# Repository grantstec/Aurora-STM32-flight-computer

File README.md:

# Aurora-STM32-flight-computer

## TO-DO
1. Finalize Parts List
2. Begin Schematic
3. Import OSH park pcb settings into KiCAD
4. Footprint demensions
5. Assemble footprint/layout
6. Traces
7. 3d Model?

## Resources
OSH park pcb setup link: https://github.com/grantstec/Aurora-STM32-flight-computer.git

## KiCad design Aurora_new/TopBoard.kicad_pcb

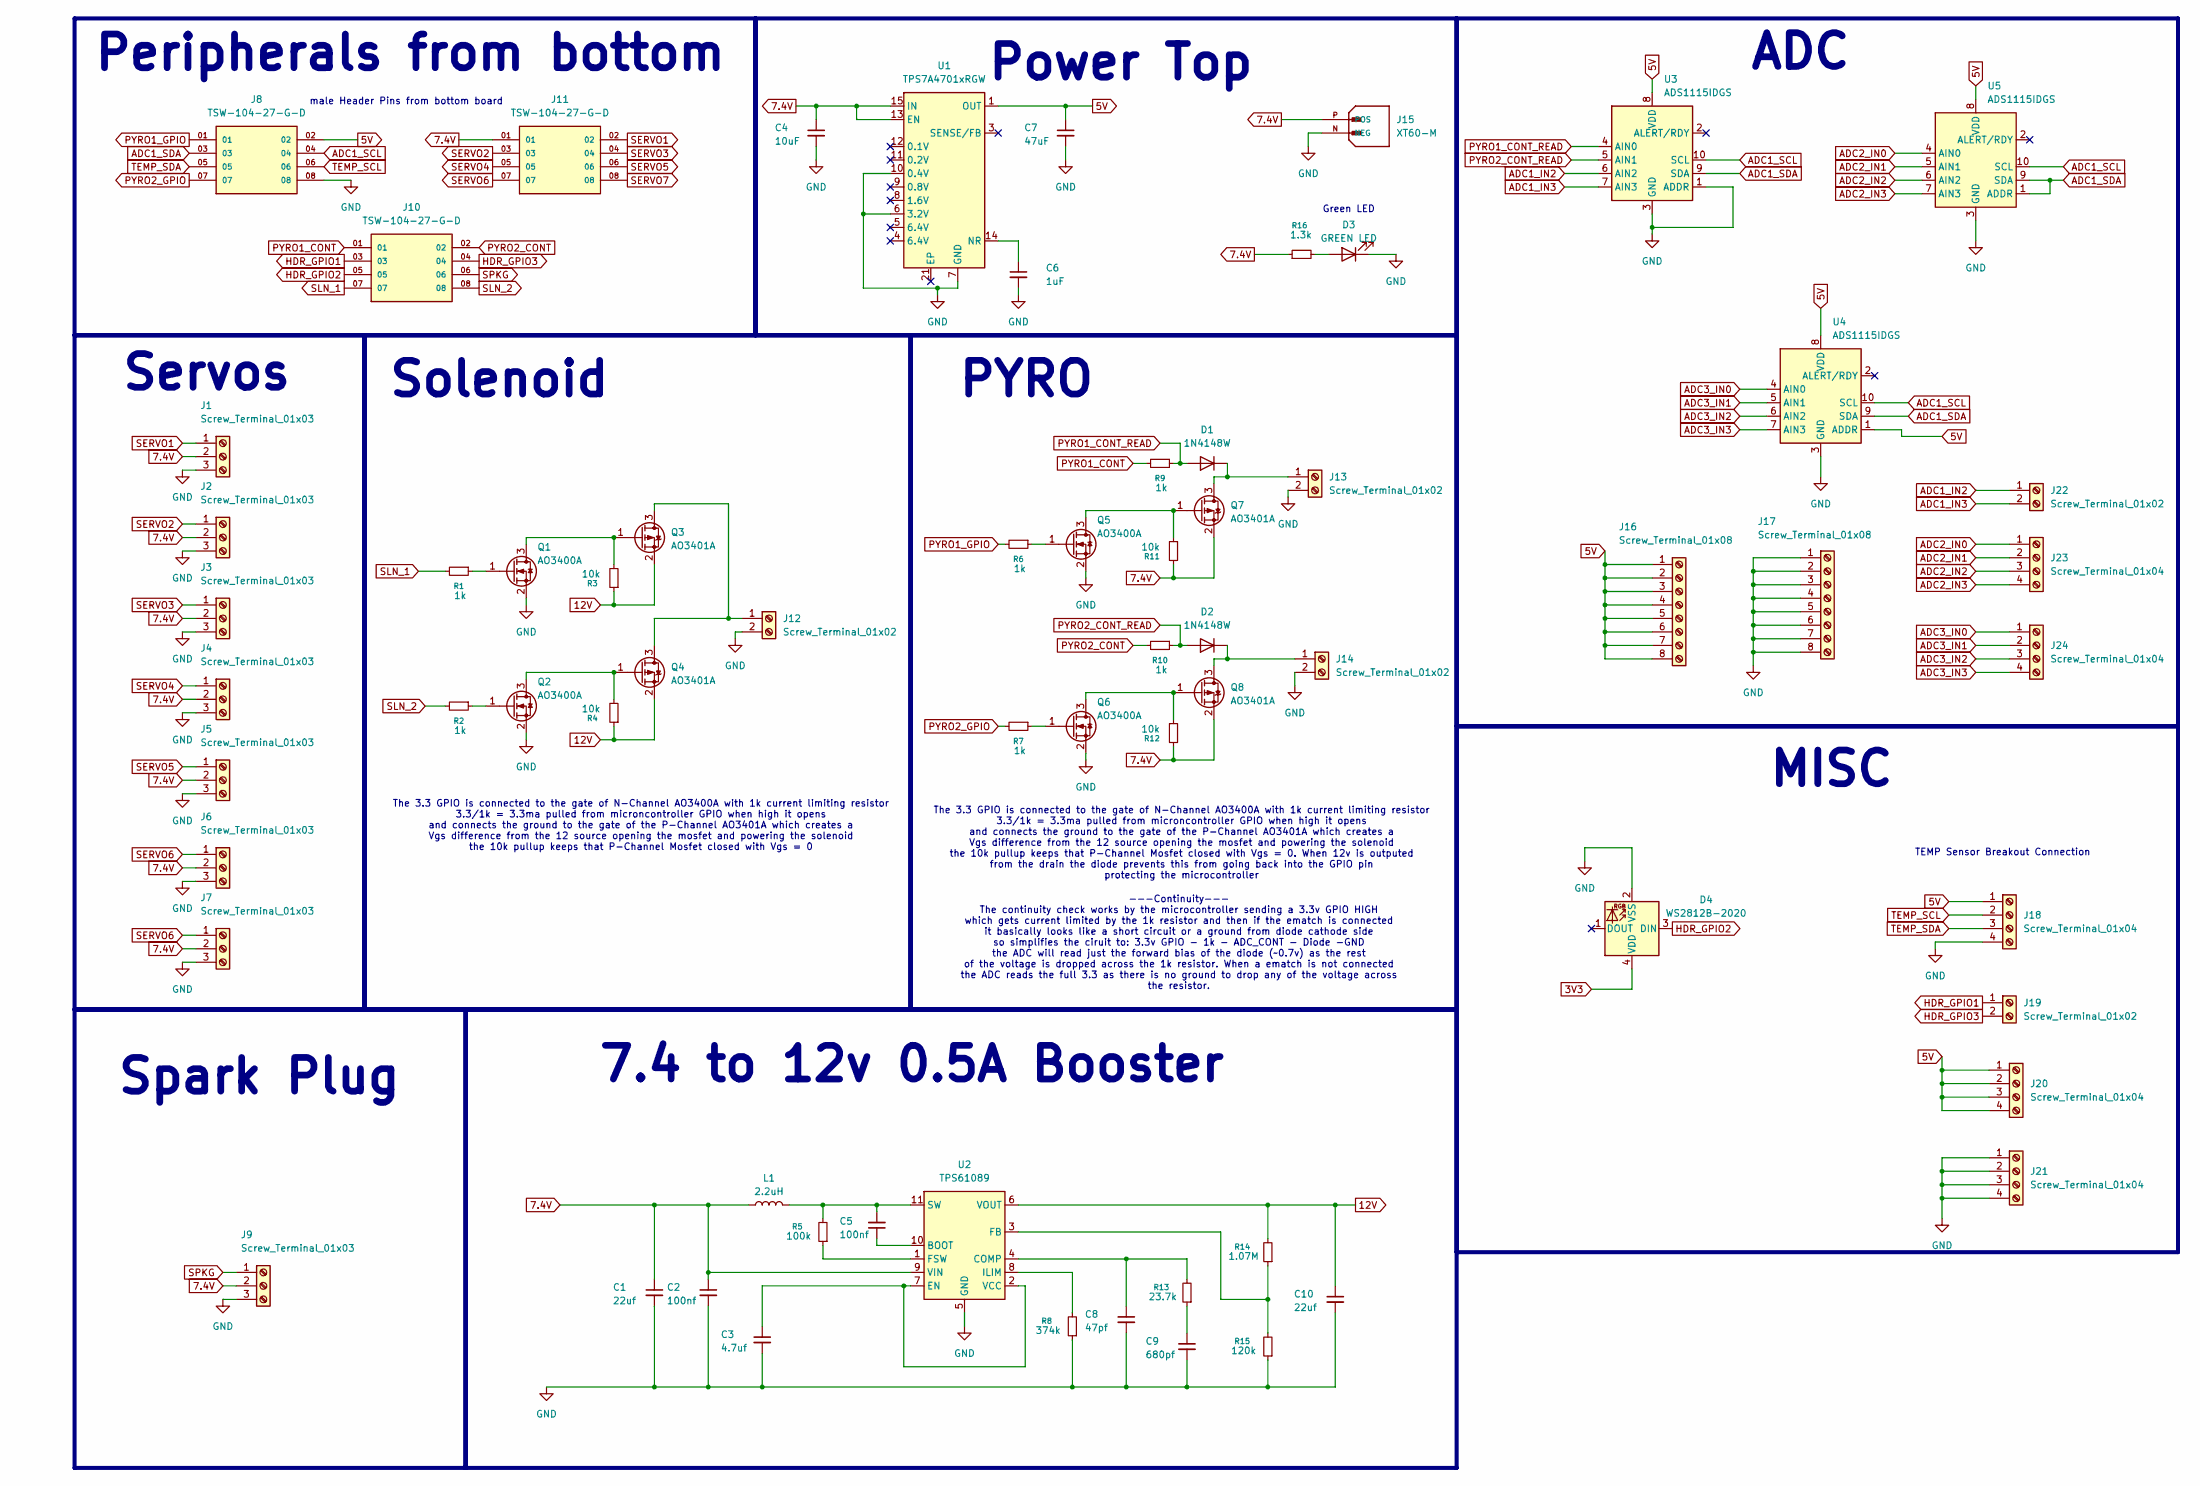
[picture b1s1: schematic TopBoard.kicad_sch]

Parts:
C1, C10: 22uf; C_0805_2012Metric
C2, C5: 100nf; C_0805_2012Metric
C3: 4.7uf; C_0805_2012Metric
C4: 10uF; C_0805_2012Metric
C6: 1uF; C_0805_2012Metric
C7: 47uF; C_0805_2012Metric
C8: 47pf; C_0805_2012Metric
C9: 680pf; C_0805_2012Metric
D1, D2: 1N4148W; D_SOD-123
D3: GREEN LED; LED_Cree-PLCC4_5x5mm_CW
D4: WS2812B-2020; LED_WS2812B-2020_PLCC4_2.0x2.0mm
J1, J2, J3, J4, J5, J6, J7, J9: Screw_Terminal_01x03; PHOENIX_1935174
J8, J10, J11: TSW-104-27-G-D; SAMTEC_TSW-104-27-G-D; PARTREV R
J12, J13, J14, J19, J22: Screw_Terminal_01x02; CONN_1729128_PXC
J15: XT60-M; AMASS_XT60-M; PARTREV V1.2
J16, J17: Screw_Terminal_01x08; CONN_1715789_PXC
J18, J20, J21, J23, J24: Screw_Terminal_01x04; CONN_1715747_PXC
L1: 2.2uH; L_0805_2012Metric
Q1, Q2, Q5, Q6: AO3400A; SOT-23
Q3, Q4, Q7, Q8: AO3401A; SOT-23
R1, R2, R6, R7, R9, R10: 1k; R_0805_2012Metric
R3, R4, R11, R12: 10k; R_0805_2012Metric
R5: 100k; R_0805_2012Metric
R8: 374k; R_0805_2012Metric
R13: 23.7k; R_0805_2012Metric
R14: 1.07M; R_0805_2012Metric
R15: 120k; R_0805_2012Metric
R16: 1.3k; R_0805_2012Metric
U1: TPS7A4701xRGW; Texas_RGW0020A_VQFN-20-1EP_5x5mm_P0.65mm_EP3.15x3.15mm
U2: TPS61089; Texas_VQFN-RNR0011A-11
U3, U4, U5: ADS1115IDGS; TSSOP-10_3x3mm_P0.5mm

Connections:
3V3: D4.4 (VDD)
5V: C7.1, J8.02, J16.1, J16.2, J16.3, J16.4, J16.5, J16.6, J16.7, J16.8, J18.1, J20.1, J20.2, J20.3, J20.4, U1.1 (OUT), U1.20 (OUT), U3.8 (VDD), U4.1 (ADDR), U4.8 (VDD), U5.8 (VDD)
7.4V: C1.1, C2.1, C4.1, J1.2, J2.2, J3.2, J4.2, J5.2, J6.2, J7.2, J9.2, J11.01, J15.P (POS), L1.1, Q7.2 (S), Q8.2 (S), R11.1, R12.1, R16.1, U1.13 (EN), U1.15 (IN), U1.16 (IN), U2.9 (VIN)
12V: C10.1, Q3.2 (S), Q4.2 (S), R3.1, R4.1, R14.2, U2.6 (VOUT)
ADC1_IN2: J22.1, U3.6 (AIN2)
ADC1_IN3: J22.2, U3.7 (AIN3)
ADC1_SCL: J8.04, U3.10 (SCL), U4.10 (SCL), U5.10 (SCL)
ADC1_SDA: J8.03, U3.9 (SDA), U4.9 (SDA), U5.1 (ADDR), U5.9 (SDA)
ADC2_IN0: J23.1, U5.4 (AIN0)
ADC2_IN1: J23.2, U5.5 (AIN1)
ADC2_IN2: J23.3, U5.6 (AIN2)
ADC2_IN3: J23.4, U5.7 (AIN3)
ADC3_IN0: J24.1, U4.4 (AIN0)
ADC3_IN1: J24.2, U4.5 (AIN1)
ADC3_IN2: J24.3, U4.6 (AIN2)
ADC3_IN3: J24.4, U4.7 (AIN3)
GND: C1.2, C2.2, C3.2, C4.2, C6.2, C7.2, C8.2, C9.2, C10.2, D3.1 (K), D4.2 (VSS), J1.3, J2.3, J3.3, J4.3, J5.3, J6.3, J7.3, J8.08, J9.3, J12.2, J13.2, J14.2, J15.N (NEG), J17.1, J17.2, J17.3, J17.4, J17.5, J17.6, J17.7, J17.8, J18.4, J21.1, J21.2, J21.3, J21.4, Q1.2 (S), Q2.2 (S), Q5.2 (S), Q6.2 (S), R8.1, R15.1, U1.6 (3.2V), U1.7 (GND), U1.10 (0.4V), U2.5 (GND), U3.1 (ADDR), U3.3 (GND), U4.3 (GND), U5.3 (GND)
HDR_GPIO1: J10.03, J19.1
HDR_GPIO2: D4.3 (DIN), J10.05
HDR_GPIO3: J10.04, J19.2
unnamed: C9.1, R13.1
unnamed: D1.1 (K), J13.1, Q7.3 (D)
unnamed: D2.1 (K), J14.1, Q8.3 (D)
unnamed: D3.2 (A), R16.2
unnamed: J12.1, Q3.3 (D), Q4.3 (D)
unnamed: Q1.3 (D), Q3.1 (G), R3.2
unnamed: Q1.1 (G), R1.1
unnamed: Q2.3 (D), Q4.1 (G), R4.2
unnamed: Q2.1 (G), R2.1
unnamed: Q5.3 (D), Q7.1 (G), R11.2
unnamed: Q5.1 (G), R6.1
unnamed: Q6.3 (D), Q8.1 (G), R12.2
unnamed: Q6.1 (G), R7.1
unnamed: C6.1, U1.14 (NR)
unnamed: C5.1, U2.10 (BOOT)
unnamed: C8.1, R13.2, U2.4 (COMP)
unnamed: C3.1, U2.2 (VCC), U2.7 (EN)
unnamed: R14.1, R15.2, U2.3 (FB)
unnamed: R5.1, U2.1 (FSW)
unnamed: R8.2, U2.8 (ILIM)
unnamed: C5.2, L1.2, R5.2, U2.11 (SW)
PYRO1_CONT: J10.01, R9.2
PYRO1_CONT_READ: D1.2 (A), R9.1, U3.4 (AIN0)
PYRO1_GPIO: J8.01, R6.2
PYRO2_CONT: J10.02, R10.2
PYRO2_CONT_READ: D2.2 (A), R10.1, U3.5 (AIN1)
PYRO2_GPIO: J8.07, R7.2
SERVO1: J1.1, J11.02
SERVO2: J2.1, J11.03
SERVO3: J3.1, J11.04
SERVO4: J4.1, J11.05
SERVO5: J5.1, J11.06
SERVO6: J6.1, J7.1, J11.07
SERVO7: J11.08
SLN_1: J10.07, R1.2
SLN_2: J10.08, R2.2
SPKG: J9.1, J10.06
TEMP_SCL: J8.06, J18.2
TEMP_SDA: J8.05, J18.3

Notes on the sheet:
ADC
Power Top
MISC
male Header Pins from bottom board
The 3.3 GPIO is connected to the gate of N-Channel AO3400A with 1k current limiting resistor 3.3/1k = 3.3ma pulled from microncontroller GPIO when high it opens and connects the ground to the gate of the P-Channel AO3401A which creates a Vgs difference from the 12 source opening the mosfet and powe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
Peripherals from bottom
PYRO
TEMP Sensor Breakout Connection
Spark Plug
The 3.3 GPIO is connected to the gate of N-Channel AO3400A with 1k current limiting resistor 3.3/1k = 3.3ma pulled from microncontroller GPIO when high it opens and connects the ground to the gate of the P-Channel AO3401A which creates a Vgs difference from the 12 source opening the mosfet and powe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
---Continuity--- The continuity check works by the microcontroller sending a 3.3v GPIO HIGH which gets current limited by the 1k resistor and then if the ematch is connected it basically looks like a short circuit or a ground from diode cathode side so simplifies the ciruit to: 3.3v GPIO - 1k - ADC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
Green LED
7.4 to 12v 0.5A Booster
Solenoid
Servos

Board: 2 copper layers, 68 parts (0 on the bottom side), 57 nets, no tracks yet.

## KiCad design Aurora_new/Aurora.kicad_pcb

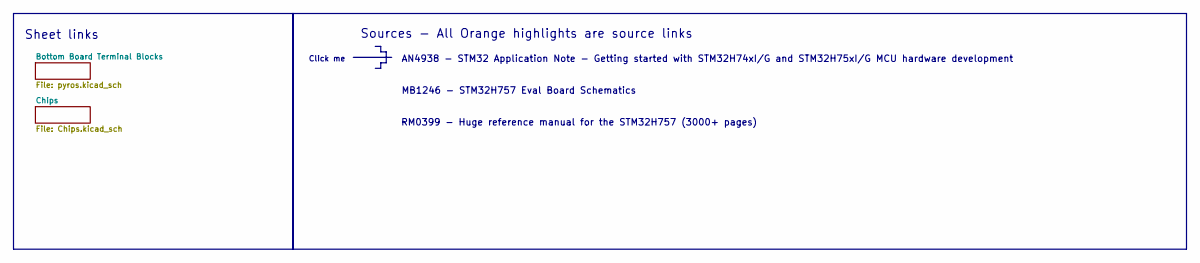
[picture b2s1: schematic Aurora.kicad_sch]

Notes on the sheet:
RM0399 - Huge reference manual for the STM32H757 (3000+ pages)
AN4938 - STM32 Application Note - Getting started with STM32H74xI/G and STM32H75xI/G MCU hardware development
MB1246 - STM32H757 Eval Board Schematics
Sheet links
Sources - All Orange highlights are source links
Click me

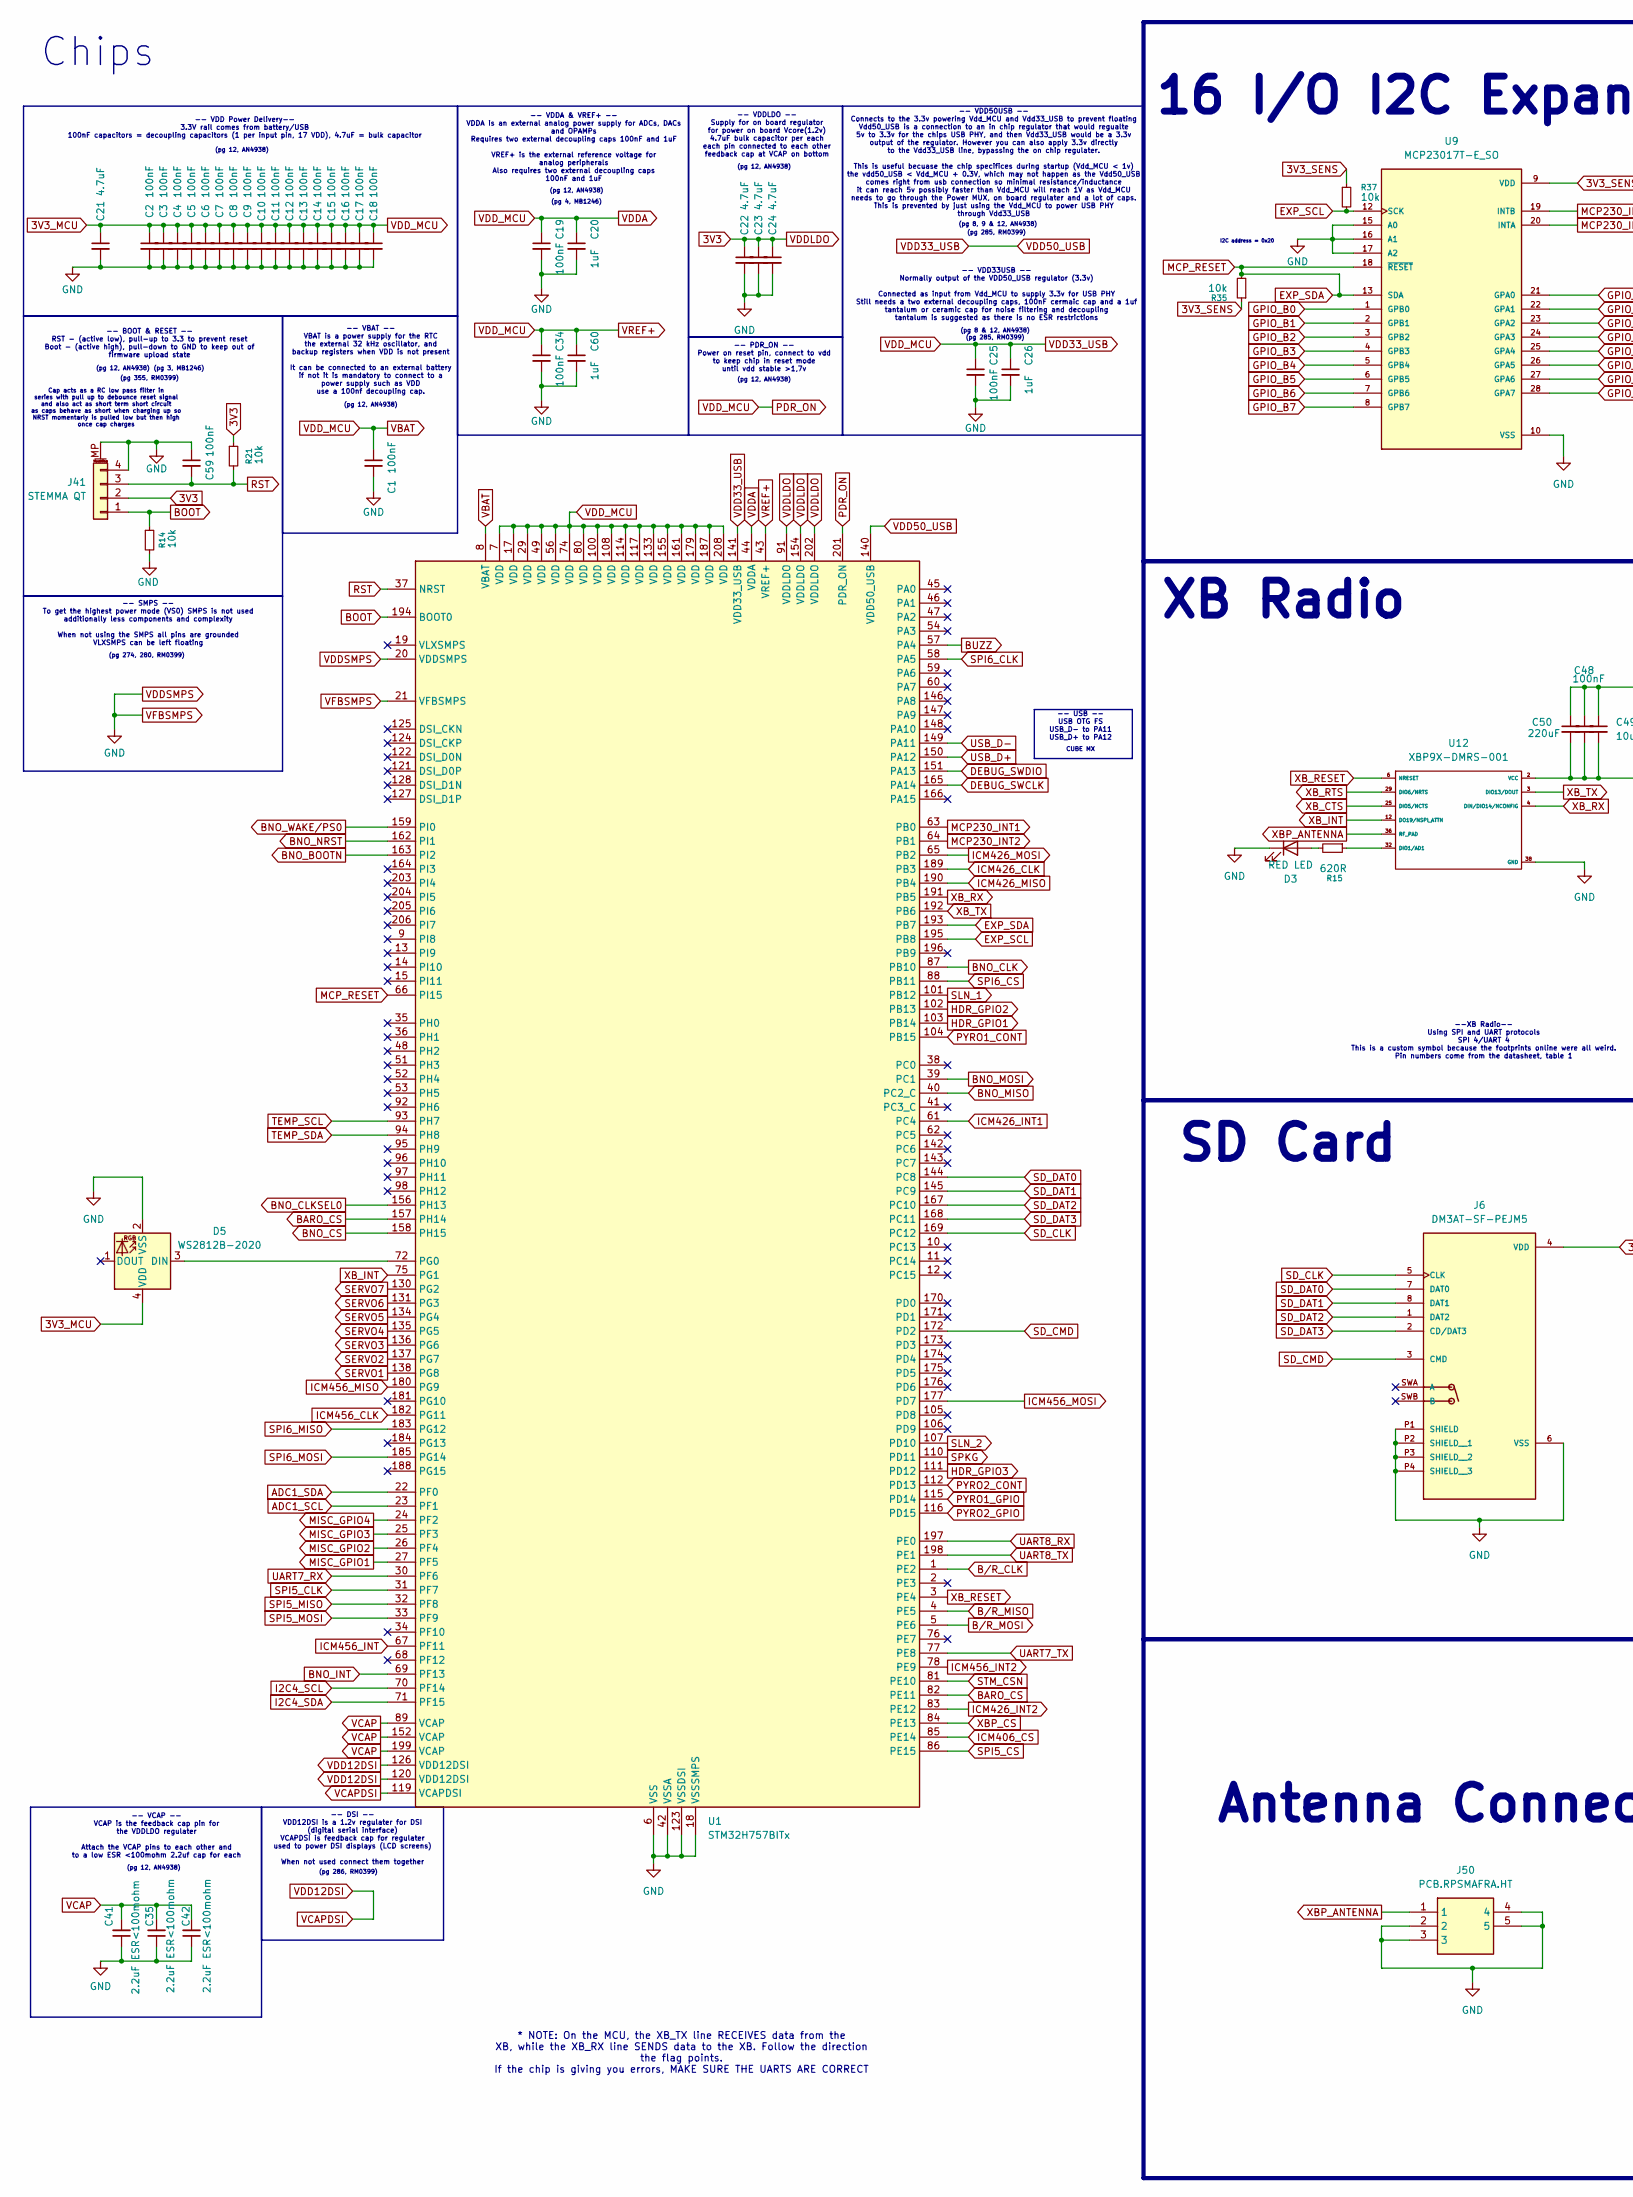
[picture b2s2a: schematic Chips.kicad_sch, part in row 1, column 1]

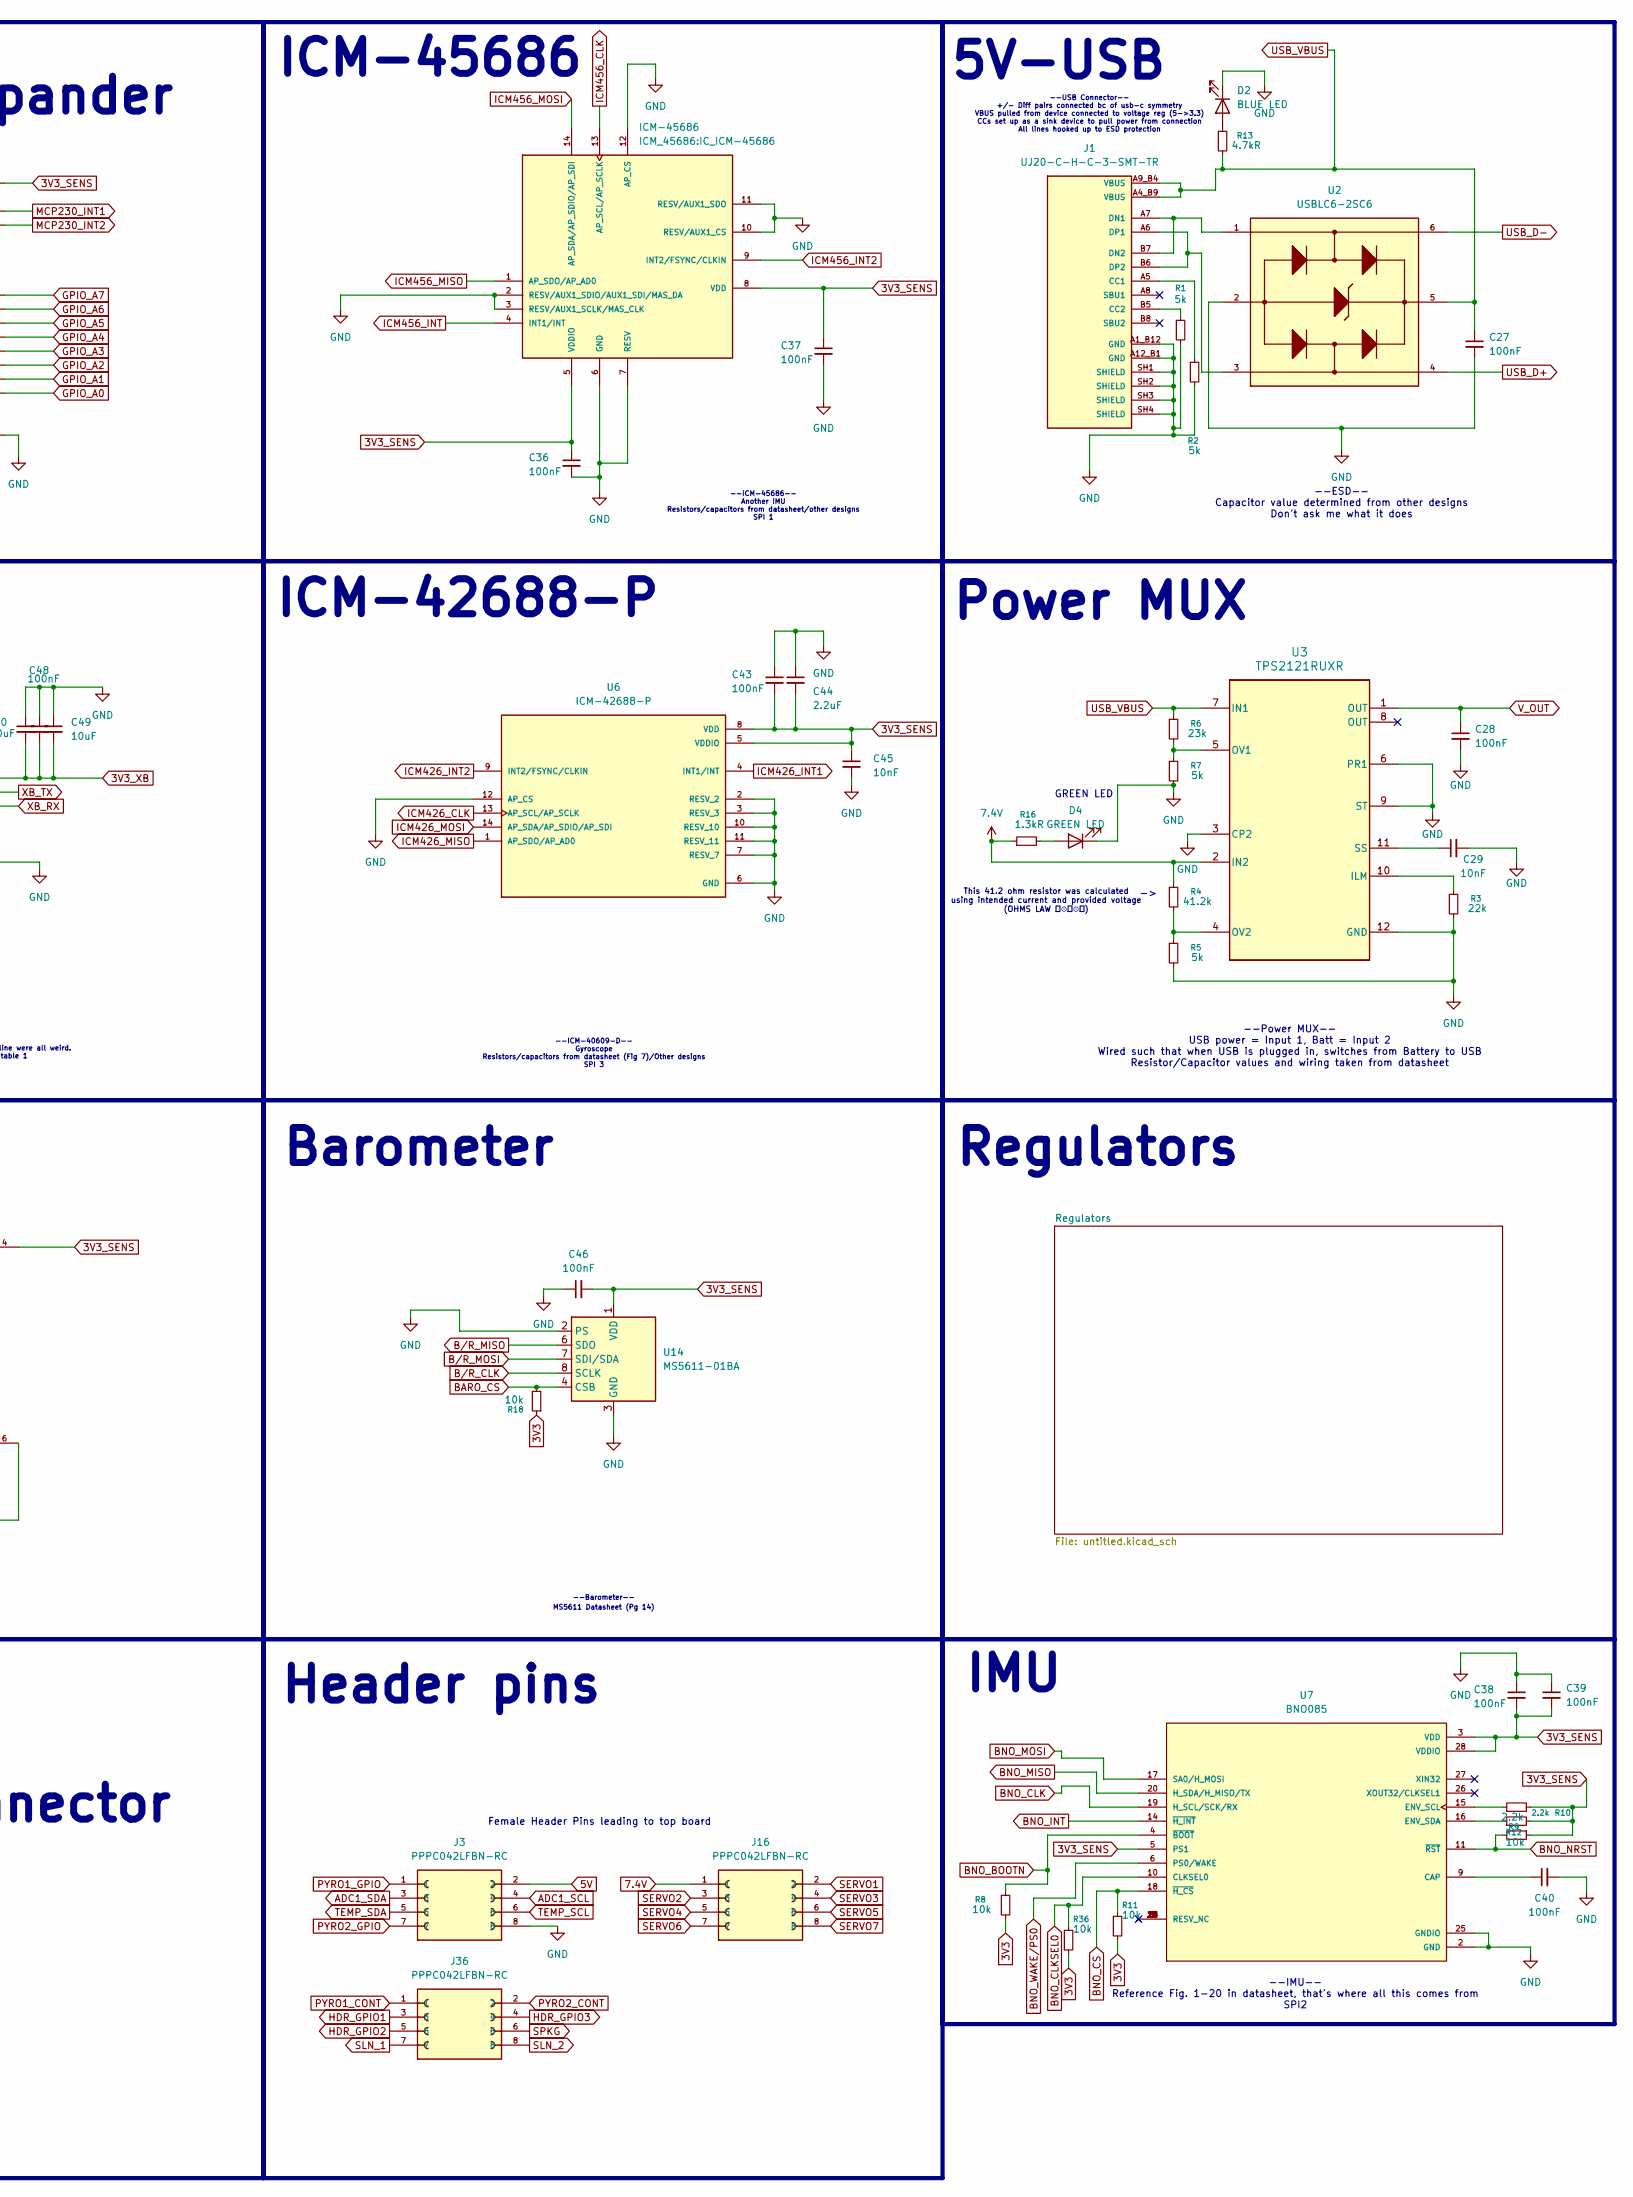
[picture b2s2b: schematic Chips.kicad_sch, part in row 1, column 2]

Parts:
C1, C2, C3, C4, C5, C6, C7, C8, C9, C10, C11, C12, C13, C14, C15, C16, C17, C18, C19, C25, C27, C28, C34, C36, C37, C38, C39, C40, C43, C46, C48, C59: 100nF; C_0805_2012Metric
C20, C26, C60: 1uF; C_0805_2012Metric
C21, C22, C23, C24: 4.7uF; C_0805_2012Metric
C29, C45: 10nF; C_0805_2012Metric
C35, C41, C42: 2.2uF ESR<100mohm; C_0805_2012Metric
C44: 2.2uF; C_0805_2012Metric
C49: 10uF; C_0805_2012Metric
C50: 220uF; C_1206_3216Metric
D2: BLUE LED; LED_Cree-PLCC4_5x5mm_CW
D3: RED LED; LED_Cree-PLCC4_5x5mm_CW
D4: GREEN LED; LED_Cree-PLCC4_5x5mm_CW
D5: WS2812B-2020; LED_WS2812B-2020_PLCC4_2.0x2.0mm
J1: UJ20-C-H-C-3-SMT-TR; CUI_UJ20-C-H-C-3-SMT-TR; PARTREV 1.0
J3, J16, J36: PPPC042LFBN-RC; SULLINS_PPPC042LFBN-RC; PARTREV L
J6: DM3AT-SF-PEJM5; HRS_DM3AT-SF-PEJM5; PARTREV 20200913
J41: STEMMA QT; JST_SH_SM04B-SRSS-TB_1x04-1MP_P1.00mm_Horizontal
J50: PCB.RPSMAFRA.HT; PCBRPSMAFRAHT; Mouser Part Number 960-PCB.RPSMAFRA.HT
R1, R2, R5, R7: 5k; R_0805_2012Metric
R3: 22k; R_0805_2012Metric
R4: 41.2k; R_0805_2012Metric
R6: 23k; R_0805_2012Metric
R8, R11, R12, R14, R18, R21, R35, R36, R37: 10k; R_0805_2012Metric
R9, R10: 2.2k; R_0805_2012Metric
R13: 4.7kR; R_0805_2012Metric
R15: 620R; R_0805_2012Metric
R16: 1.3kR; R_0805_2012Metric
U1: STM32H757BITx; LQFP-208_28x28mm_P0.5mm
U2: USBLC6-2SC6; SOT95P280X145-6N
U3: TPS2121RUXR; RUX0012A
U5: ICM-45686; IC_ICM-45686; PARTREV 0.2
U6: ICM-42688-P; PQFN50P300X250X97-14N; PARTREV 1.2
U7: BNO085; IC_BNO085; PARTREV v1.17
U9: MCP23017T-E_SO; SOIC127P1030X265-28N
U12: XBP9X-DMRS-001; XCVR_XBP9X-DMUS-021
U14: MS5611-01BA; LGA-8_3x5mm_P1.25mm

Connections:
3V3: C22.1, C23.1, C24.1, J41.2, R8.2, R11.2, R18.1, R21.1, R36.2, U1.91 (VDDLDO), U1.154 (VDDLDO), U1.202 (VDDLDO); also elsewhere on the board
3V3_MCU: C1.1, C2.1, C3.1, C4.1, C5.1, C6.1, C7.1, C8.1, C9.1, C10.1, C11.1, C12.1, C13.1, C14.1, C15.1, C16.1, C17.1, C18.1, C19.1, C20.1, C21.1, C25.1, C26.1, C34.1, C60.1, D5.4 (VDD), U1.7 (VDD), U1.8 (VBAT), U1.17 (VDD), U1.29 (VDD), U1.43 (VREF+), U1.44 (VDDA), U1.49 (VDD), U1.56 (VDD), U1.74 (VDD), U1.80 (VDD), U1.100 (VDD), U1.108 (VDD), U1.114 (VDD), U1.117 (VDD), U1.133 (VDD), U1.140 (VDD50_USB), U1.141 (VDD33_USB), U1.155 (VDD), U1.161 (VDD), U1.179 (VDD), U1.187 (VDD), U1.201 (PDR_ON), U1.208 (VDD); also elsewhere on the board
3V3_SENS: C36.1, C37.1, C38.2, C39.2, C43.2, C44.2, C45.1, C46.2, J6.4 (VDD), R9.2, R10.2, R12.1, R35.1, R37.1, U5.5 (VDDIO), U5.8 (VDD), U6.5 (VDDIO), U6.8 (VDD), U7.3 (VDD), U7.5 (PS1), U7.28 (VDDIO), U9.9 (VDD), U14.1 (VDD); also elsewhere on the board
3V3_XB: C48.2, C49.2, C50.2, U12.2 (VCC); also elsewhere on the board
5V: J3.2
7.4V: J16.1, R4.1, R16.1, U3.2 (IN2)
ADC1_SCL: J3.4, U1.23 (PF1)
ADC1_SDA: J3.3, U1.22 (PF0)
BARO_CS: R18.2, U1.82 (PE11), U1.157 (PH14), U14.4 (CSB), U14.5 (CSB)
BNO_BOOTN: R8.1, U1.163 (PI2), U7.4 (~BOOT)
BNO_CLK: U1.87 (PB10), U7.19 (H_SCL/SCK/RX)
BNO_CLKSEL0: R36.1, U1.156 (PH13), U7.10 (CLKSEL0)
BNO_CS: R11.1, U1.158 (PH15), U7.18 (~H_CS)
BNO_INT: U1.69 (PF13), U7.14 (~H_INT)
BNO_MISO: U1.40 (PC2_C), U7.20 (H_SDA/H_MISO/TX)
BNO_MOSI: U1.39 (PC1), U7.17 (SA0/H_MOSI)
BNO_NRST: R12.2, U1.162 (PI1), U7.11 (~RST)
BNO_WAKE/PS0: U1.159 (PI0), U7.6 (PS0/WAKE)
BOOT: J41.1, R14.1, U1.194 (BOOT0)
BUZZ: U1.57 (PA4); also elsewhere on the board
B/R_CLK: U1.1 (PE2), U14.8 (SCLK)
B/R_MISO: U1.4 (PE5), U14.6 (SDO)
B/R_MOSI: U1.5 (PE6), U14.7 (SDI/SDA)
DEBUG_SWCLK: U1.165 (PA14); also elsewhere on the board
DEBUG_SWDIO: U1.151 (PA13); also elsewhere on the board
EXP_SCL: R37.2, U1.195 (PB8), U9.12 (SCK)
EXP_SDA: R35.2, U1.66 (PI15), U1.193 (PB7), U9.13 (SDA), U9.18 (~RESET)
GPIO_A0: U9.28 (GPA7); also elsewhere on the board
GPIO_A1: U9.27 (GPA6); also elsewhere on the board
GPIO_A2: U9.26 (GPA5); also elsewhere on the board
GPIO_A3: U9.25 (GPA4); also elsewhere on the board
GPIO_A4: U9.24 (GPA3); also elsewhere on the board
GPIO_A5: U9.23 (GPA2); also elsewhere on the board
GPIO_A6: U9.22 (GPA1); also elsewhere on the board
GPIO_A7: U9.21 (GPA0); also elsewhere on the board
GPIO_B0: U9.1 (GPB0); also elsewhere on the board
GPIO_B1: U9.2 (GPB1); also elsewhere on the board
GPIO_B2: U9.3 (GPB2); also elsewhere on the board
GPIO_B3: U9.4 (GPB3); also elsewhere on the board
GPIO_B4: U9.5 (GPB4); also elsewhere on the board
GPIO_B5: U9.6 (GPB5); also elsewhere on the board
GPIO_B6: U9.7 (GPB6); also elsewhere on the board
GPIO_B7: U9.8 (GPB7); also elsewhere on the board
HDR_GPIO1: J36.3, U1.103 (PB14)
HDR_GPIO2: J36.5, U1.102 (PB13)
HDR_GPIO3: J36.4, U1.111 (PD12)
I2C4_SCL: U1.70 (PF14); also elsewhere on the board
I2C4_SDA: U1.71 (PF15); also elsewhere on the board
ICM406_CS: U1.85 (PE14)
ICM426_CLK: U1.189 (PB3), U6.13 (AP_SCL/AP_SCLK)
ICM426_INT1: U1.61 (PC4), U6.4 (INT1/INT)
ICM426_INT2: U1.83 (PE12), U6.9 (INT2/FSYNC/CLKIN)
ICM426_MISO: U1.190 (PB4), U6.1 (AP_SDO/AP_AD0)
ICM426_MOSI: U1.65 (PB2), U6.14 (AP_SDA/AP_SDIO/AP_SDI)
ICM456_CLK: U1.182 (PG11), U5.13 (AP_SCL/AP_SCLK)
ICM456_INT: U1.67 (PF11), U5.4 (INT1/INT)
ICM456_INT2: U1.78 (PE9), U5.9 (INT2/FSYNC/CLKIN)
ICM456_MISO: U1.180 (PG9), U5.1 (AP_SDO/AP_AD0)
ICM456_MOSI: U1.177 (PD7), U5.14 (AP_SDA/AP_SDIO/AP_SDI)
MCP230_INT1: U1.63 (PB0), U9.19 (INTB)
MCP230_INT2: U1.64 (PB1), U9.20 (INTA)
MISC_GPIO1: U1.27 (PF5); also elsewhere on the board
MISC_GPIO2: U1.26 (PF4); also elsewhere on the board
MISC_GPIO3: U1.25 (PF3); also elsewhere on the board
MISC_GPIO4: U1.24 (PF2); also elsewhere on the board
unnamed: D2.2 (A), R13.1
unnamed: D3.2 (A), R15.2
unnamed: D4.2 (A), R16.2
unnamed: D5.3 (DIN), U1.72 (PG0)
unnamed: J1.A5 (CC1), R2.1
unnamed: J1.B5 (CC2), R1.1
unnamed: J1.A7 (DN1), J1.B7 (DN2), U2.1
unnamed: J1.A6 (DP1), J1.B6 (DP2), U2.3
unnamed: R3.1, U3.10 (ILM)
unnamed: R6.2, R7.1, U3.5 (OV1)
unnamed: R4.2, R5.1, U3.4 (OV2)
unnamed: C29.1, U3.11 (SS)
unnamed: C40.1, U7.9 (CAP)
unnamed: R10.1, U7.15 (ENV_SCL)
unnamed: R9.1, U7.16 (ENV_SDA)
unnamed: R15.1, U12.32 (DIO1/AD1)
PYRO1_CONT: J36.1, U1.104 (PB15)
PYRO1_GPIO: J3.1, U1.115 (PD14)
PYRO2_CONT: J36.2, U1.112 (PD13)
PYRO2_GPIO: J3.7, U1.116 (PD15)
RST: C59.2, J41.3, R21.2, U1.37 (NRST)
SD_CLK: J6.5 (CLK), U1.169 (PC12)
SD_CMD: J6.3 (CMD), U1.172 (PD2)
SD_DAT0: J6.7 (DAT0), U1.144 (PC8)
SD_DAT1: J6.8 (DAT1), U1.145 (PC9)
SD_DAT2: J6.1 (DAT2), U1.167 (PC10)
SD_DAT3: J6.2 (CD/DAT3), U1.168 (PC11)
SERVO1: J16.2, U1.138 (PG8)
SERVO2: J16.3, U1.137 (PG7)
SERVO3: J16.4, U1.136 (PG6)
SERVO4: J16.5, U1.135 (PG5)
SERVO5: J16.6, U1.134 (PG4)
SERVO6: J16.7, U1.131 (PG3)
SERVO7: J16.8, U1.130 (PG2)
SLN_1: J36.7, U1.101 (PB12)
SLN_2: J36.8, U1.107 (PD10)
SPI5_CLK: U1.31 (PF7); also elsewhere on the board
SPI5_CS: U1.86 (PE15); also elsewhere on the board
SPI5_MISO: U1.32 (PF8); also elsewhere on the board
SPI5_MOSI: U1.33 (PF9); also elsewhere on the board
SPI6_CLK: U1.58 (PA5); also elsewhere on the board
SPI6_CS: U1.88 (PB11); also elsewhere on the board
SPI6_MISO: U1.183 (PG12); also elsewhere on the board
SPI6_MOSI: U1.185 (PG14); also elsewhere on the board
SPKG: J36.6, U1.110 (PD11)
STM_CSN: U1.81 (PE10)
TEMP_SCL: J3.6, U1.93 (PH7)
TEMP_SDA: J3.5, U1.94 (PH8)
UART7_RX: U1.30 (PF6); also elsewhere on the board
UART7_TX: U1.77 (PE8); also elsewhere on the board
UART8_RX: U1.197 (PE0); also elsewhere on the board
UART8_TX: U1.198 (PE1); also elsewhere on the board
USB_D+: U1.150 (PA12), U2.4
USB_D-: U1.149 (PA11), U2.6
USB_VBUS: C27.1, J1.A4_B9 (VBUS), J1.A9_B4 (VBUS), R6.1, R13.2, U2.5, U3.7 (IN1); also elsewhere on the board
VCAP: C35.2, C41.2, C42.2, U1.89 (VCAP), U1.152 (VCAP), U1.199 (VCAP)
VCAPDSI: U1.119 (VCAPDSI), U1.120 (VDD12DSI), U1.126 (VDD12DSI)
VDDSMPS: C1.2, C2.2, C3.2, C4.2, C5.2, C6.2, C7.2, C8.2, C9.2, C10.2, C11.2, C12.2, C13.2, C14.2, C15.2, C16.2, C17.2, C18.2, C19.2, C20.2, C21.2, C22.2, C23.2, C24.2, C25.2, C26.2, C27.2, C28.2, C29.2, C34.2, C35.1, C36.2, C37.2, C38.1, C39.1, C40.2, C41.1, C42.1, C43.1, C44.1, C45.2, C46.1, C48.1, C49.1, C50.1, C59.1, C60.2, D2.1 (K), D3.1 (K), D4.1 (K), D5.2 (VSS), J1.A1_B12 (GND), J1.A12_B1 (GND), J1.SH1 (SHIELD), J1.SH2 (SHIELD), J1.SH3 (SHIELD), J1.SH4 (SHIELD), J3.8, J6.6 (VSS), J6.P1 (SHIELD), J6.P2 (SHIELD__1), J6.P3 (SHIELD__2), J6.P4 (SHIELD__3), J41.4, J41.MP (MountPin), J50.2, J50.3, J50.4, J50.5, R1.2, R2.2, R3.2, R5.2, R7.2, R14.2, U1.6 (VSS), U1.16 (VSS), U1.18 (VSSSMPS), U1.20 (VDDSMPS), U1.21 (VFBSMPS), U1.28 (VSS), U1.42 (VSSA), U1.50 (VSS), U1.55 (VSS), U1.73 (VSS), U1.79 (VSS), U1.90 (VSS), U1.99 (VSS), U1.109 (VSS), U1.113 (VSS), U1.118 (VSS), U1.123 (VSSDSI), U1.129 (VSSDSI), U1.132 (VSS), U1.139 (VSS), U1.153 (VSS), U1.160 (VSS), U1.178 (VSS), U1.186 (VSS), U1.200 (VSS), U1.207 (VSS), U2.2, U3.3 (CP2), U3.6 (PR1), U3.9 (ST), U3.12 (GND), U5.2 (RESV/AUX1_SDIO/AUX1_SDI/MAS_DA), U5.3 (RESV/AUX1_SCLK/MAS_CLK), U5.6 (GND), U5.7 (RESV), U5.10 (RESV/AUX1_CS), U5.11 (RESV/AUX1_SDO), U5.12 (AP_CS), U6.2 (RESV_2), U6.3 (RESV_3), U6.6 (GND), U6.7 (RESV_7), U6.10 (RESV_10), U6.11 (RESV_11), U6.12 (AP_CS), U7.2 (GND), U7.25 (GNDIO), U9.10 (VSS), U9.15 (A0), U9.16 (A1), U9.17 (A2), U12.38 (GND), U14.2 (PS), U14.3 (GND); also elsewhere on the board
V_OUT: C28.1, U3.1 (OUT); also elsewhere on the board
XBP_ANTENNA: J50.1, U12.36 (RF_PAD)
XBP_CS: U1.84 (PE13)
XB_CTS: U12.25 (DIO5/NCTS); also elsewhere on the board
XB_INT: U1.75 (PG1), U12.12 (DO19/NSPI_ATTN)
XB_RESET: U1.3 (PE4), U12.6 (NRESET)
XB_RTS: U12.29 (DIO6/NRTS); also elsewhere on the board
XB_RX: U1.191 (PB5), U12.4 (DIN/DIO14/NCONFIG); also elsewhere on the board
XB_TX: U1.192 (PB6), U12.3 (DIO13/DOUT); also elsewhere on the board

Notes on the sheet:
(pg 12, AN4938)
(pg 4, MB1246)
XB Radio
--XB Radio-- Using SPI and UART protocols SPI 4/UART 4 This is a custom symbol because the footprints online were all weird. Pin numbers come from the datasheet, table 1
-- VDDA & VREF+ -- VDDA is an external analog power supply for ADCs, DACs and OPAMPs Requires two external decoupling caps 100nF and 1uF VREF+ is the external reference voltage for analog peripherals Also requires two external decoupling caps 100nF and 1uF
-- PDR_ON -- Power on reset pin, connect to vdd to keep chip in reset mode until vdd stable >1,7v
--Power MUX-- USB power = Input 1, Batt = Input 2 Wired such that when USB is plugged in, switches from Battery to USB Resistor/Capacitor values and wiring taken from datasheet
-- VDD50USB -- Connects to the 3.3v powering Vdd_MCU and Vdd33_USB to prevent floating Vdd50_USB is a connection to an in chip regulator that would regualte 5v to 3.3v for the chips USB PHY, and then Vdd33_USB would be a 3.3v output of the regulator. However you can also apply 3.3v directly to the 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
ICM-42688-P
Barometer
--Barometer--
(pg 8, 9 & 12, AN4938)
(pg 285, RM0399)
GREEN LED
Header pins
--IMU-- Reference Fig. 1-20 in datasheet, that's where all this comes from SPI2
* NOTE: On the MCU, the XB_TX line RECEIVES data from the XB, while the XB_RX line SENDS data to the XB. Follow the direction the flag points. If the chip is giving you errors, MAKE SURE THE UARTS ARE CORRECT
-- VDD Power Delivery-- 3.3V rail comes from battery/USB 100nF capacitors = decoupling capacitors (1 per input pin, 17 VDD), 4.7uF = bulk capacitor
Power MUX
-- VBAT -- VBAT is a power supply for the RTC the external 32 kHz oscillator, and backup registers when VDD is not present It can be connected to an external battery if not it is mandatory to connect to a power supply such as VDD use a 100nf decoupling cap.
CUBE MX
(pg 12, AN4938)
--ESD-- Capacitor value determined from other designs Don't ask me what it does
(pg 355, RM0399)
(pg 3, MB1246)
Female Header Pins leading to top board
--ICM-40609-D-- Gyroscope Resistors/capacitors from datasheet (Fig 7)/Other designs SPI 3
MS5611 Datasheet (Pg 14)
--USB Connector-- +/- Diff pairs connected bc of usb-c symmetry VBUS pulled from device connected to voltage reg (5->3.3) CCs set up as a sink device to pull power from connection All lines hooked up to ESD protection
Antenna Connector
Regulators
-- VCAP -- VCAP is the feedback cap pin for the VDDLDO regulater Attach the VCAP pins to each other and to a low ESR <100mohm 2.2uf cap for each
This 41.2 ohm resistor was calculated using intended current and provided voltage (OHMS LAW （⊙ｏ⊙）)
I2C address = 0x20
IMU
(pg 274, 280, RM0399)
(pg 286, RM0399)
-- VDDLDO -- Supply for on board regulator for power on board Vcore(1.2v) 4.7uF bulk capacitor per each each pin connected to each other feedback cap at VCAP on bottom
(pg 8 & 12, AN4938)
-- VDD33USB -- Normally output of the VDD50_USB regulator (3.3v) Connected as input from Vdd_MCU to supply 3.3v for USB PHY Still needs a two external decoupling caps, 100nF cermaic cap and a 1uf tantalum or ceramic cap for noise filtering and decoupling tantalum is suggested as there is no ESR res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
